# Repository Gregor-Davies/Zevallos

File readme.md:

The complete files to construct your own zevallos greenpower car. All files are provided as is under the GPL 3 license with no guarantee of any of it going together smoothley. 

## Speed controller

- The speed controller is based off a raspberry pico W with four different drive modes selected through a toggle switcg, the idea of the 4 different driver modes is to allow for the optimal performance for the car in time trails and endurance races.
- The total cost of the PCBS to build is about £80 inlcuding the bare pcbs and all the parts. Mine were kindly funded by hackclubs onboard.
- The speed controller also has built in datalogging of motor current, motor voltage, battery current and battery voltage with a RPM module in the works for the nect update.

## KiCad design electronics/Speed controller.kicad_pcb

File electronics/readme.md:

All the electronics and production files for the project.

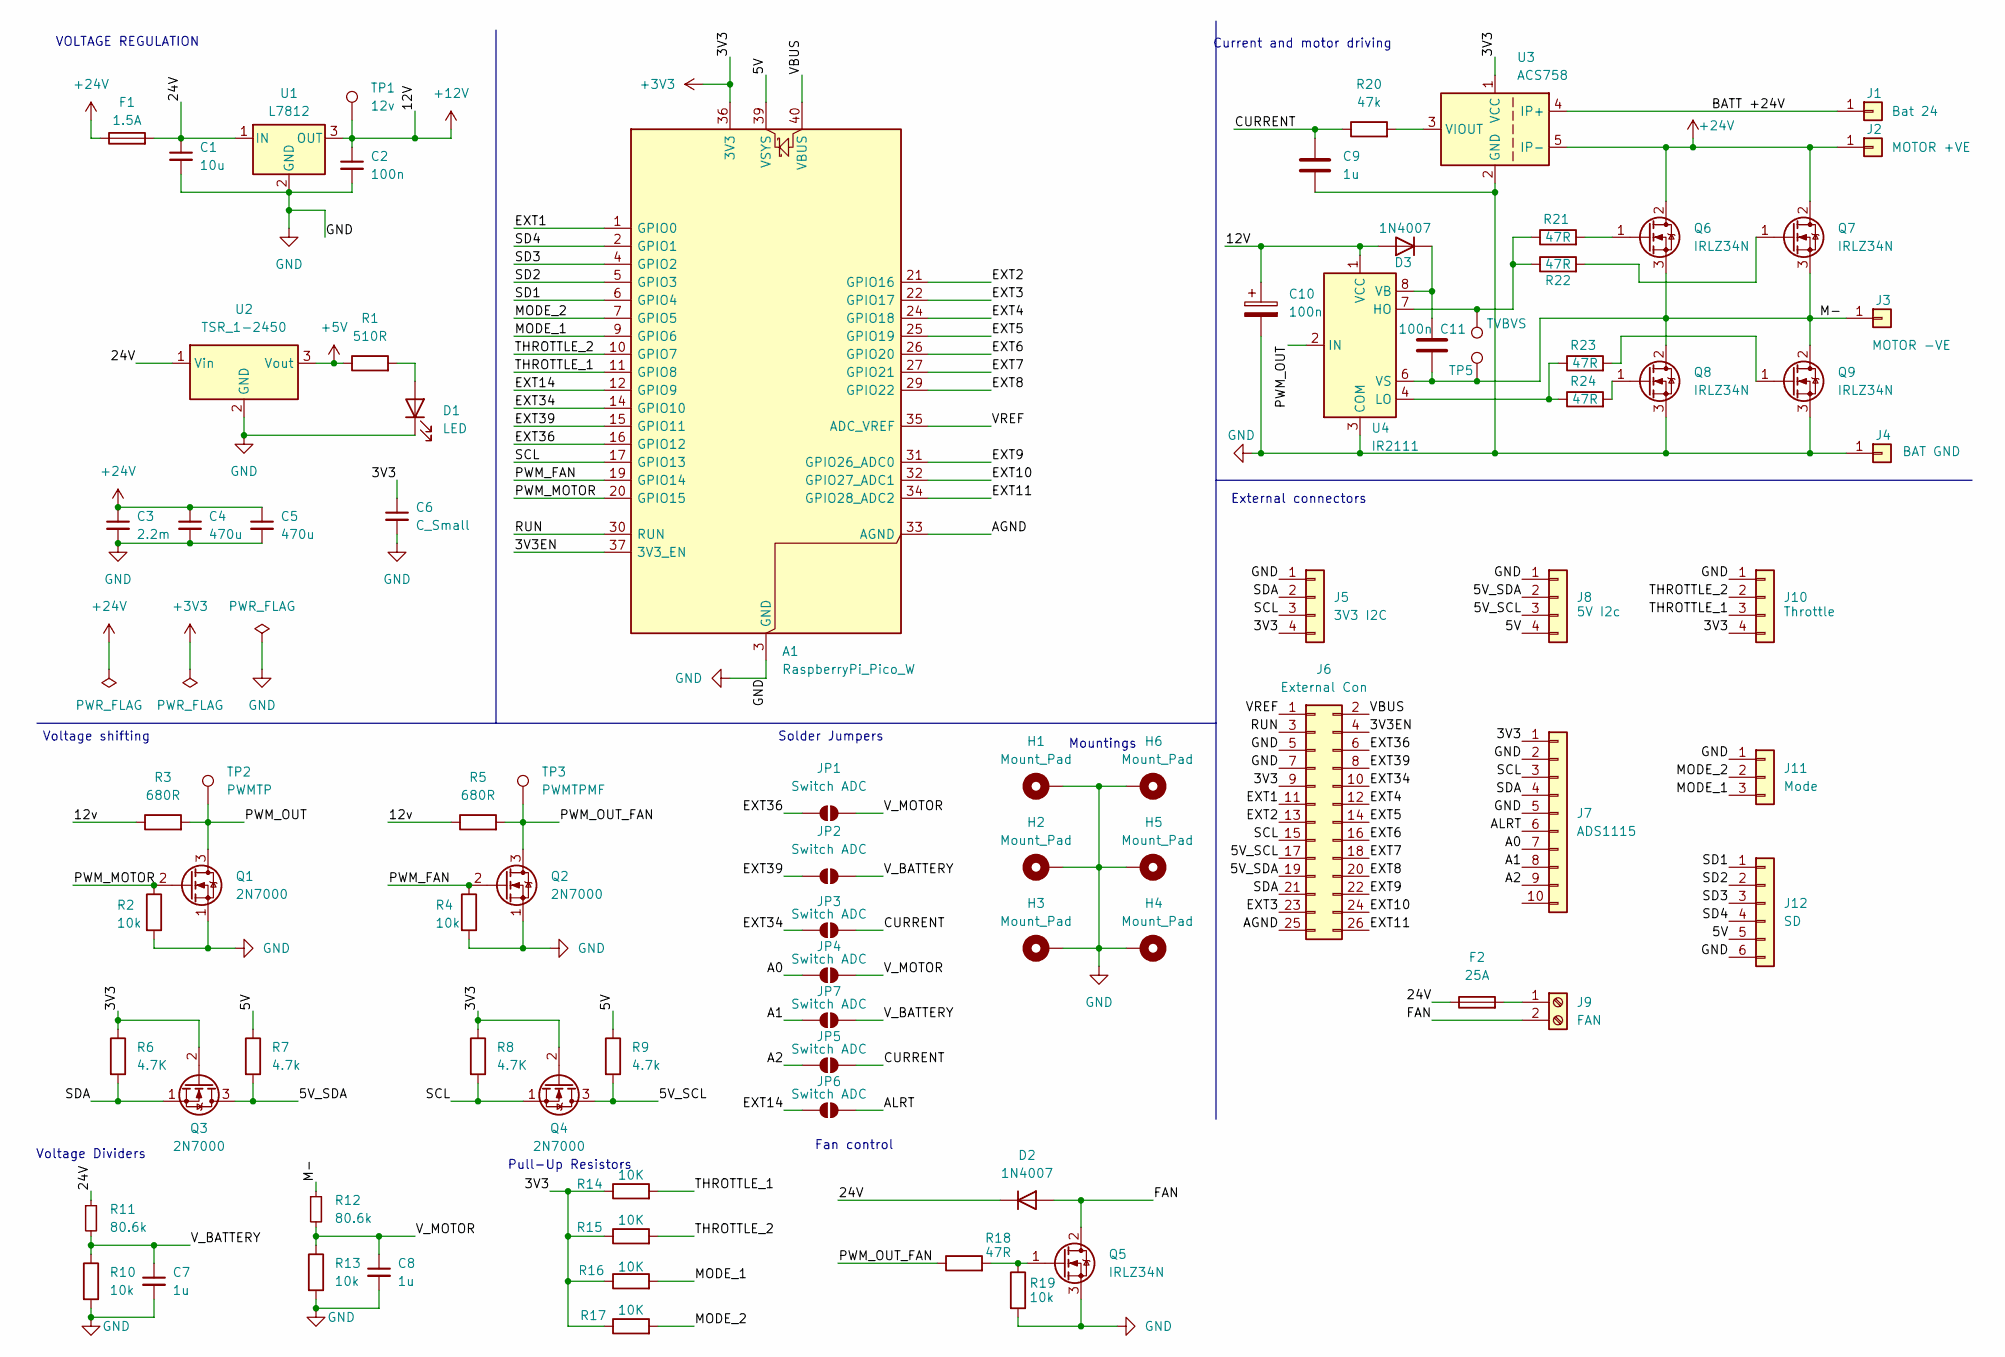
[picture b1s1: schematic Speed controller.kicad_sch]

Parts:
A1: RaspberryPi_Pico_W; RaspberryPi_Pico_Common
C1: 10u
C2, C10, C11: 100n
C3: 2.2m
C4, C5: 470u
C6: C_Small
C7, C8, C9: 1u
D1: LED
D2, D3: 1N4007; D_DO-41_SOD81_P10.16mm_Horizontal
F1: 1.5A
F2: 25A
H1, H2, H3, H4, H5, H6: Mount_Pad
J1: Bat 24
J2: MOTOR +VE
J3: MOTOR -VE
J4: BAT GND
J5: 3V3 I2C
J6: External Con
J7: ADS1115
J8: 5V I2c
J9: FAN
J10: Throttle
J11: Mode
J12: SD
JP1, JP2, JP3, JP4, JP5, JP6, JP7: Switch ADC
Q1, Q2, Q3, Q4: 2N7000; TO-92_Inline
Q5, Q6, Q7, Q8, Q9: IRLZ34N; TO-220-3_Vertical
R1: 510R
R2, R4, R10, R13, R19: 10k
R3, R5: 680R
R6, R8: 4.7K
R7, R9: 4.7k
R11, R12: 80.6k
R14, R15, R16, R17: 10K
R18, R21, R22, R23, R24: 47R
R20: 47k
TP1: 12v
TP2: PWMTP
TP3: PWMTPMF
TP4: TVBVS
TP5: TestPoint
U1: L7812
U2: TSR_1-2450; Converter_DCDC_TRACO_TSR-1_THT
U3: ACS758; Allegro_CB_PFF
U4: IR2111

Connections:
+3V3: A1.36 (3V3), C6.1, J5.4, J6.9, J7.1, J10.4, Q3.2 (G), Q4.2 (G), R6.1, R8.1, R14.1, R15.1, R16.1, R17.1, U3.1 (VCC)
+5V: R1.1, U2.3 (Vout)
+12V: C2.1, C10.1, D3.2 (A), R3.1, R5.1, TP1.1, U1.3 (OUT), U4.1 (VCC)
+24V: C3.1, C4.1, C5.1, F1.1, J2.1, Q6.2 (D), Q7.2 (D), U3.5 (IP-)
/3V3EN: A1.37 (3V3_EN), J6.4
/5V: A1.39 (VSYS), J8.4, J12.5, R7.1, R9.1
/5V_SCL: J6.17, J8.3, Q4.3 (D), R9.2
/5V_SDA: J6.19, J8.2, Q3.3 (D), R7.2
/24V: C1.1, D2.1 (K), F1.2, F2.1, R11.1, U1.1 (IN), U2.1 (Vin)
/A0: J7.7, JP4.1 (A)
/A1: J7.8, JP7.1 (A)
/A2: J7.9, JP5.1 (A)
/AGND: A1.33 (AGND), J6.25
/ALRT: J7.6, JP6.2 (B)
/BATT +24V: J1.1, U3.4 (IP+)
/EXT1: A1.1 (GPIO0), J6.11
/EXT2: A1.21 (GPIO16), J6.13
/EXT3: A1.22 (GPIO17), J6.23
/EXT4: A1.24 (GPIO18), J6.12
/EXT5: A1.25 (GPIO19), J6.14
/EXT6: A1.26 (GPIO20), J6.16
/EXT7: A1.27 (GPIO21), J6.18
/EXT8: A1.29 (GPIO22), J6.20
/EXT9: A1.31 (GPIO26_ADC0), J6.22
/EXT10: A1.32 (GPIO27_ADC1), J6.24
/EXT11: A1.34 (GPIO28_ADC2), J6.26, J7.10
/EXT14: A1.12 (GPIO9), JP6.1 (A)
/EXT34: A1.14 (GPIO10), J6.10, JP3.1 (A)
/EXT36: A1.16 (GPIO12), J6.6, JP1.1 (A)
/EXT39: A1.15 (GPIO11), J6.8, JP2.1 (A)
/FAN: D2.2 (A), J9.2, Q5.2 (D)
/M-: C11.2, J3.1, Q6.3 (S), Q7.3 (S), Q8.2 (D), Q9.2 (D), R12.1, TP5.1, U4.6 (VS)
/MODE_1: A1.9 (GPIO6), J11.3, R16.2
/MODE_2: A1.7 (GPIO5), J11.2, R17.2
/PWM_FAN: A1.19 (GPIO14), Q2.2 (G), R4.1
/PWM_MOTOR: A1.20 (GPIO15), Q1.2 (G), R2.1
/PWM_OUT: Q1.3 (D), R3.2, TP2.1, U4.2 (IN)
/PWM_OUT_FAN: Q2.3 (D), R5.2, R18.1, TP3.1
/RUN: A1.30 (RUN), J6.3
/SCL: A1.17 (GPIO13), J5.3, J6.15, J7.3, Q4.1 (S), R8.2
/SD1: A1.6 (GPIO4), J12.1
/SD2: A1.5 (GPIO3), J12.2
/SD3: A1.4 (GPIO2), J12.3
/SD4: A1.2 (GPIO1), J12.4
/SDA: J5.2, J6.21, J7.4, Q3.1 (S), R6.2
/THROTTLE_1: A1.11 (GPIO8), J10.3, R14.2
/THROTTLE_2: A1.10 (GPIO7), J10.2, R15.2
/VBUS: A1.40 (VBUS), J6.2
/VREF: A1.35 (ADC_VREF), J6.1
/V_BATTERY: C7.1, JP2.2 (B), JP7.2 (B), R10.1, R11.2
/V_MOTOR: C8.1, JP1.2 (B), JP4.2 (B), R12.2, R13.1
GND: A1.3 (GND), A1.8 (GND), A1.13 (GND), A1.18 (GND), A1.23 (GND), A1.28 (GND), A1.38 (GND), C1.2, C2.2, C3.2, C4.2, C5.2, C6.2, C7.2, C8.2, C9.2, C10.2, D1.1 (K), H1.1, H2.1, H3.1, H4.1, H5.1, H6.1, J4.1, J5.1, J6.5, J6.7, J7.2, J7.5, J8.1, J10.1, J11.1, J12.6, Q1.1 (S), Q2.1 (S), Q5.3 (S), Q8.3 (S), Q9.3 (S), R2.2, R4.2, R10.2, R13.2, R19.2, U1.2 (GND), U2.2 (GND), U3.2 (GND), U4.3 (COM); also elsewhere on the board
unnamed: D1.2 (A), R1.2
unnamed: C11.1, D3.1 (K), U4.8 (VB)
unnamed: F2.2, J9.1
unnamed: Q5.1 (G), R18.2, R19.1
unnamed: Q6.1 (G), R21.2
unnamed: Q7.1 (G), R22.2
unnamed: Q8.1 (G), R24.2
unnamed: Q9.1 (G), R23.2
unnamed: R21.1, R22.1, TP4.1, U4.7 (HO)
unnamed: R23.1, R24.1, U4.4 (LO)

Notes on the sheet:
Pull-Up Resistors
Voltage Dividers
Fan control
Solder Jumpers
Voltage shifting
Current and motor driving
VOLTAGE REGULATION
Mountings
External connectors

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
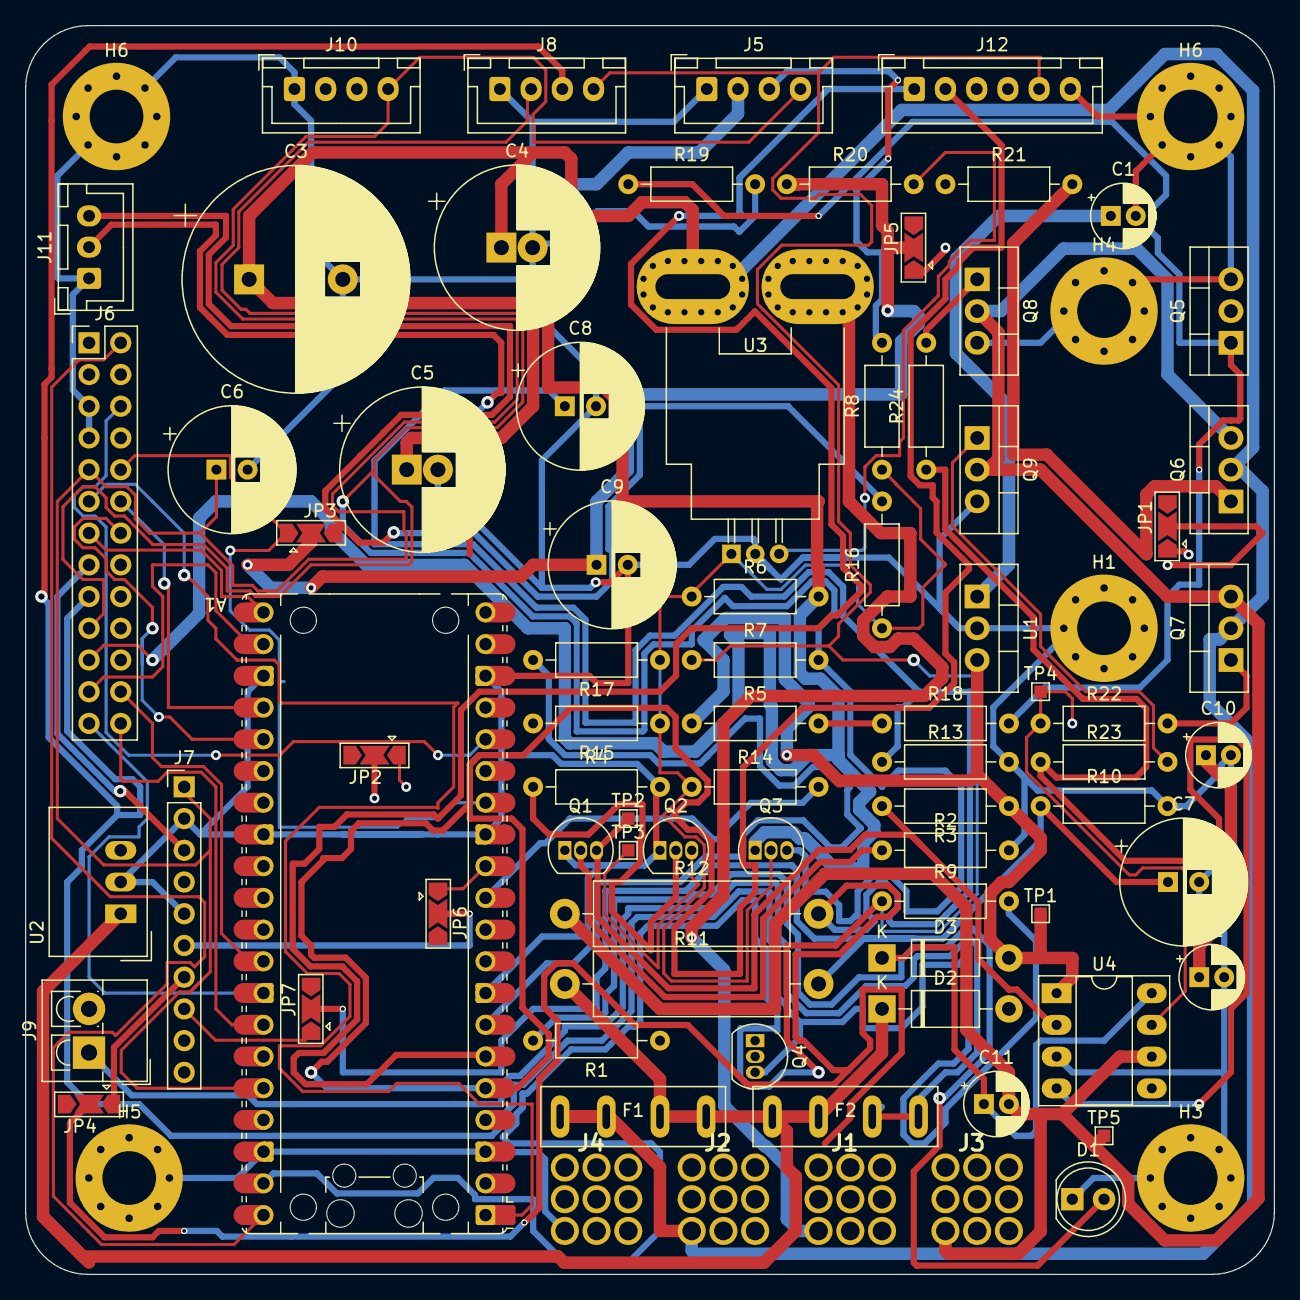
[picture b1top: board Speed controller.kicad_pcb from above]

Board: 4 copper layers, 100.0 x 100.0 mm, 84 parts (0 on the bottom side), 63 nets.

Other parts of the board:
H6#2: Mount_Pad; MountingHole_4.3mm_M4_Pad_Via

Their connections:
GND: H6#2.1; also elsewhere on the board

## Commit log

2024-06-21 Create LICENSE
2024-06-21 Schematic done
2024-07-13 Routing done
